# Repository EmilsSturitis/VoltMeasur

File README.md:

# VoltMeasur
4ch 0-10V adc with ADS1248

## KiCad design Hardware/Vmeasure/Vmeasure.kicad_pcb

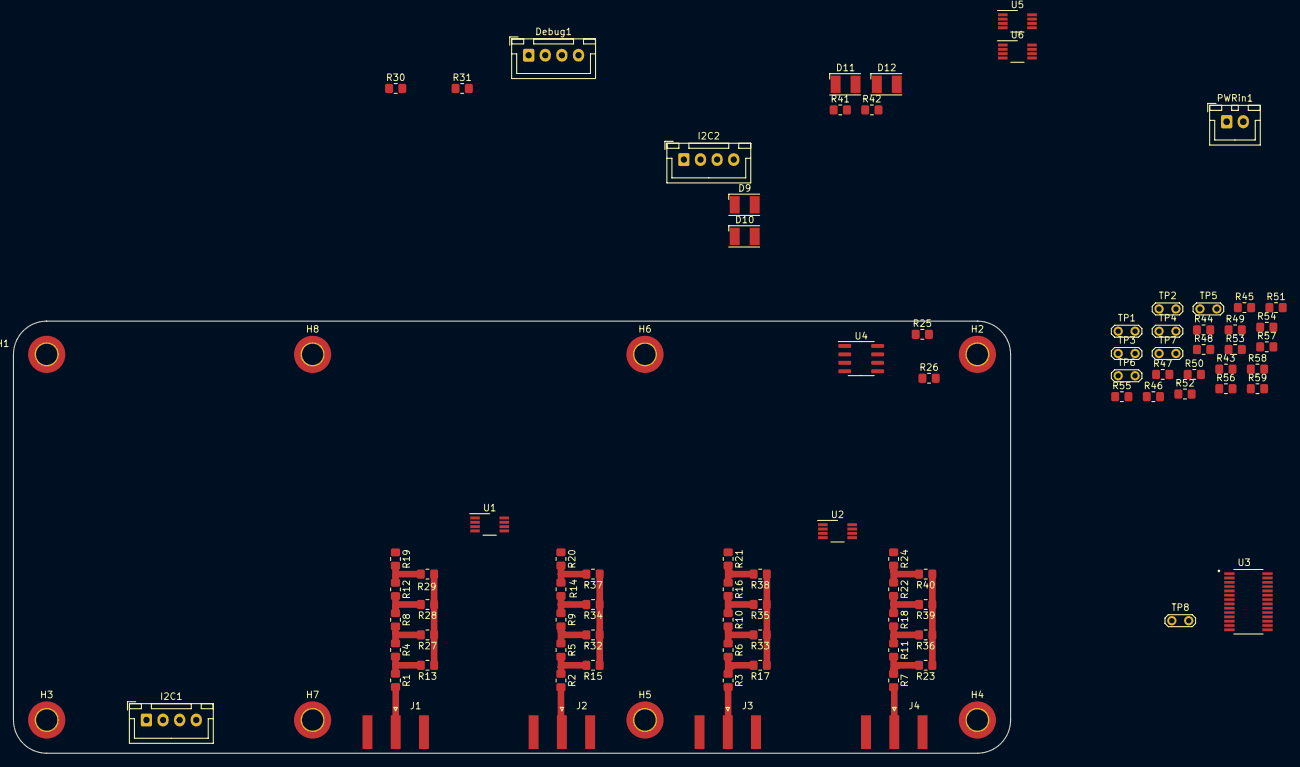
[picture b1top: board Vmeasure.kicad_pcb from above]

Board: 2 copper layers, 150.0 x 65.0 mm, 94 parts (1 on the bottom side), 70 nets.

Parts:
D9, D10, D11, D12: LED; LED_PLCC-2
Debug1: Conn_01x04; JST_XH_B4B-XH-A_1x04_P2.50mm_Vertical
H1, H2, H3, H4, H5, H6, H7, H8: MountingHole; MountingHole_3.2mm_M3_DIN965_Pad_TopBottom
I2C1, I2C2: Conn_01x04; JST_XH_B4B-XH-A_1x04_P2.50mm_Vertical
J1, J2, J3, J4: Conn_Coaxial; SMA_Amphenol_132289_EdgeMount
PWRin1: Conn_01x02; JST_XH_B2B-XH-A_1x02_P2.50mm_Vertical
R1, R2, R3, R7: 9M; R_0805_2012Metric_Pad1.20x1.40mm_HandSolder
R4, R5, R6, R11: 900K; R_0805_2012Metric_Pad1.20x1.40mm_HandSolder
R8, R9, R10, R18, R25, R26: 90K; R_0805_2012Metric_Pad1.20x1.40mm_HandSolder
R12, R14, R16, R22: 9K; R_0805_2012Metric_Pad1.20x1.40mm_HandSolder
R13, R15, R17, R23, R27, R28, R29, R30, R31, R32, R33, R34, R35, R36, R37, R38, R39, R40, R41, R42, R47, R48, R49, R50, R53, R54, R55, R56: 0R; R_0805_2012Metric_Pad1.20x1.40mm_HandSolder
R19, R20, R21, R24: 1K; R_0805_2012Metric_Pad1.20x1.40mm_HandSolder
R43, R44, R45, R46, R51, R52, R57, R59: 47R; R_0805_2012Metric_Pad1.20x1.40mm_HandSolder
R58: 470k; R_0805_2012Metric_Pad1.20x1.40mm_HandSolder
TP1, TP2, TP3, TP4, TP5, TP6, TP7, TP8: TestPoint_2Pole; TestPoint_2Pads_Pitch2.54mm_Drill0.8mm
U1, U2, U5, U6: OPA2333xxDGK; VSSOP-8_3.0x3.0mm_P0.65mm
U3: ADS1248IPWR; SOP65P640X120-28N
U4: REF5040AD; SOIC-8_3.9x4.9mm_P1.27mm
U7: SC0915; MODULE_SC0915

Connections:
AIN0: R53.2, U5.1, U5.2
AIN1: R47.2, U1.1, U1.2
AIN2: R54.2, U5.6, U5.7
AIN3: R48.2, U1.6, U1.7
AIN4: R55.2, U6.1, U6.2
AIN5: R49.2, U2.1, U2.2
AIN6: R56.2, U6.6, U6.7
AIN7: R50.2, U2.6, U2.7
GNDA: TP1.1, TP2.1, TP3.1, TP4.1, TP5.1, TP6.1, TP7.1, TP8.1, U3.21
GNDD: D9.1, D10.1, D11.1, D12.1, U3.2, U7.3, U7.8, U7.13, U7.18, U7.23, U7.28, U7.38, U7.D2
IEXC1: TP2.2, U3.20
IEXC2: TP3.2, U3.19
unnamed: J1.1, R1.2
unnamed: J1.2, R19.1
unnamed: J2.1, R2.2
unnamed: J2.2, R20.1
unnamed: J3.1, R3.2
unnamed: J3.2, R21.1
unnamed: J4.1, R7.2
unnamed: J4.2, R24.1
unnamed: R13.1, R27.1, R28.1, R29.1, U1.3
unnamed: R15.1, R32.1, R34.1, R37.1, U1.5
unnamed: R17.1, R33.1, R35.1, R38.1, U2.3
unnamed: R23.1, R36.1, R39.1, R40.1, U2.5
unnamed: D9.2, R30.2
unnamed: D10.2, R31.2
unnamed: D11.2, R41.2
unnamed: D12.2, R42.2
unnamed: R1.1, R4.2, R13.2
unnamed: R10.1, R16.2, R35.2
unnamed: R6.1, R10.2, R33.2
unnamed: R11.1, R18.2, R36.2
unnamed: R7.1, R11.2, R23.2
unnamed: R12.1, R19.2, R29.2
unnamed: R8.1, R12.2, R28.2
unnamed: R14.1, R20.2, R37.2
unnamed: R9.1, R14.2, R34.2
unnamed: R2.1, R5.2, R15.2
unnamed: R16.1, R21.2, R38.2
unnamed: R3.1, R6.2, R17.2
unnamed: R18.1, R22.2, R39.2
unnamed: R22.1, R24.2, R40.2
unnamed: R25.1, U4.6
unnamed: R25.2, R26.1, U5.3, U5.5, U6.3, U6.5
unnamed: R26.2, U4.4
unnamed: R4.1, R8.2, R27.2
unnamed: R5.1, R9.2, R32.2
unnamed: R43.1, U3.27
unnamed: R44.1, U3.3
unnamed: R45.1, U3.4
unnamed: R46.1, U3.23
unnamed: R47.1, U3.12
unnamed: R48.1, U3.18
unnamed: R49.1, U3.14
unnamed: R50.1, U3.16
unnamed: R51.1, U3.24
unnamed: R52.1, U3.28
unnamed: R53.1, U3.11
unnamed: R54.1, U3.17
unnamed: R55.1, U3.13
unnamed: R56.1, U3.15
unnamed: R57.2, U3.25
unnamed: R59.2, U3.26
unnamed: U7.A, U7.B, U7.C, U7.D
REFN0: TP4.2, U3.6
REFN1: TP8.2, U3.8
REFP0: TP1.2, U3.5
REFP1: TP7.2, U3.7
VREFCOM: TP5.2, U3.10
VREFOUT: TP6.2, U3.9

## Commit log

2022-07-24 PCB outline and connector placement
2022-07-26 little update
